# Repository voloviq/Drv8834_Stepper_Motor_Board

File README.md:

# Drv8834_Stepper_Motor_Board
Simple dump pcb and schematic - dump due to obtain 3d design of module

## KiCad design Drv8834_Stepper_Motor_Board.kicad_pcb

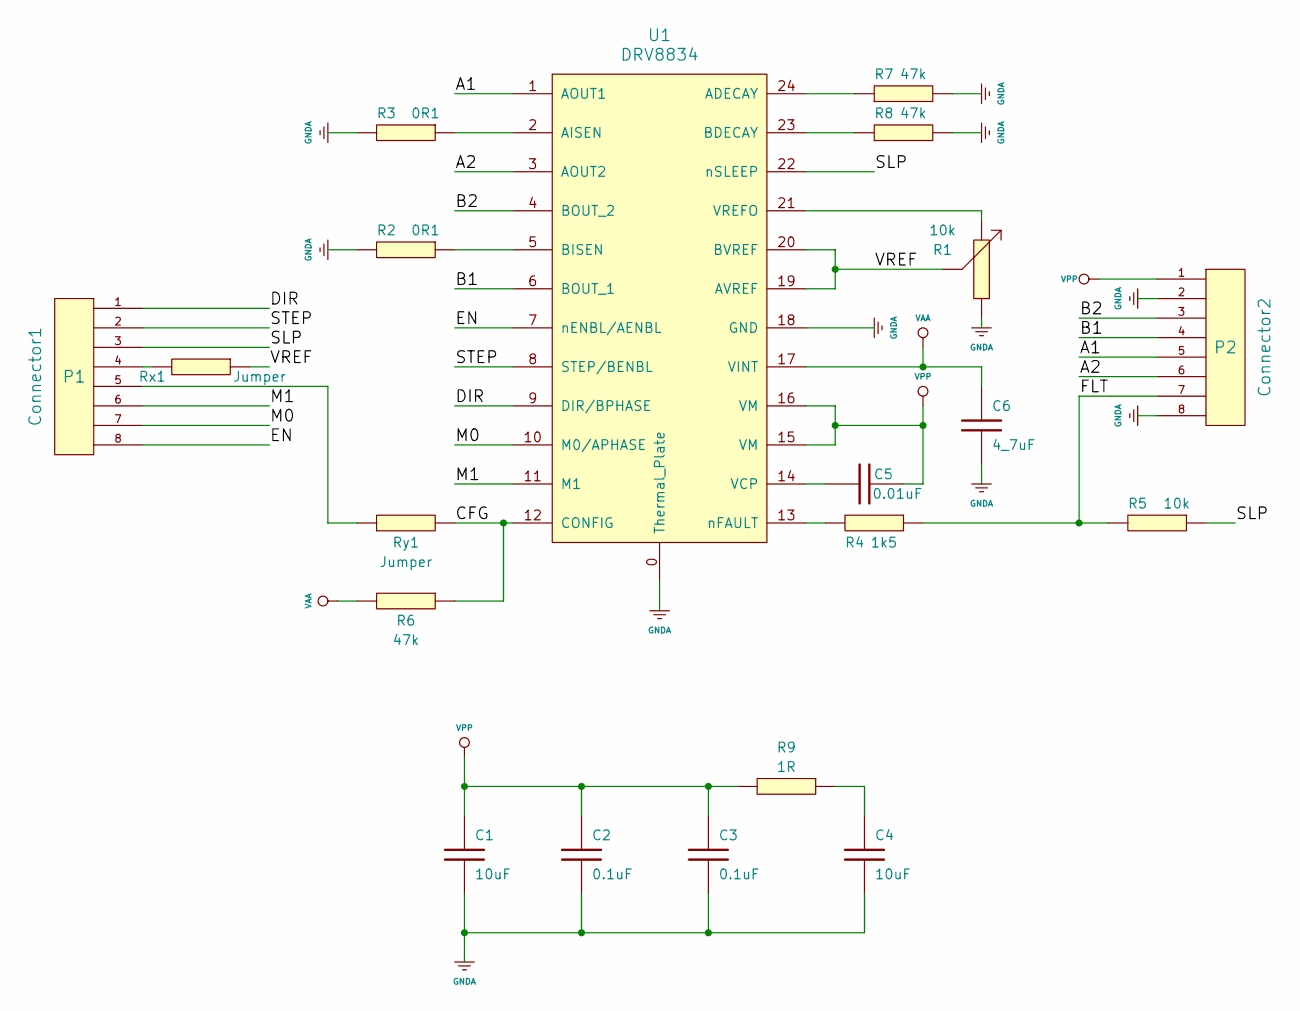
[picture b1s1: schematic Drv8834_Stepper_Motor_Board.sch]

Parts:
C1, C4: 10uF; 10uF_0805
C2, C3: 0.1uF; 100nF_0603
C5: 0.01uF; 1nF_0603
C6: 4_7uF; 4_7uF_0603
P1: Connector1; Goldpin_8_2_54mm
P2: Connector2; Goldpin_8_2_54mm
R1: 10k; 3364X-1-103E
R2, R3: 0R1; 0R1_1206
R4: 1k5; 1k5_0603
R5: 10k; 10k_0603
R6, R7, R8: 47k; 47k_0603
R9: 1R; 1R_0603
Rx1: Jumper; 0R_0603
Ry1: Jumper; 0R_0603
U1: DRV8834; DRV8834_QFN24

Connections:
/A1: P2.5, U1.1 (AOUT1)
/A2: P2.6, U1.3 (AOUT2)
/B1: P2.4, U1.6 (BOUT_1)
/B2: P2.3, U1.4 (BOUT_2)
/CFG: R6.1, Ry1.2, U1.12 (CONFIG)
/DIR: P1.1, U1.9 (DIR/BPHASE)
/EN: P1.8, U1.7 (nENBL/AENBL)
/FLT: P2.7, R4.1, R5.2
/M0: P1.7, U1.10 (M0/APHASE)
/M1: P1.6, U1.11 (M1)
/SLP: P1.3, R5.1, U1.22 (nSLEEP)
/STEP: P1.2, U1.8 (STEP/BENBL)
/VREF: R1.2, Rx1.1, U1.19 (AVREF), U1.20 (BVREF)
GNDA: C1.2, C2.2, C3.2, C4.2, C6.2, P2.2, P2.8, R1.1, R2.2, R3.2, R7.2, R8.2, U1.0 (Thermal_Plate), U1.18 (GND)
unnamed: C4.1, R9.1
unnamed: C5.1, U1.14 (VCP)
unnamed: P1.4, Rx1.2
unnamed: P1.5, Ry1.1
unnamed: R1.3, U1.21 (VREFO)
unnamed: R2.1, U1.5 (BISEN)
unnamed: R3.1, U1.2 (AISEN)
unnamed: R4.2, U1.13 (nFAULT)
unnamed: R7.1, U1.24 (ADECAY)
unnamed: R8.1, U1.23 (BDECAY)
VAA: C6.1, R6.2, U1.17 (VINT)
VPP: C1.1, C2.1, C3.1, C5.2, P2.1, R9.2, U1.15 (VM), U1.16 (VM)

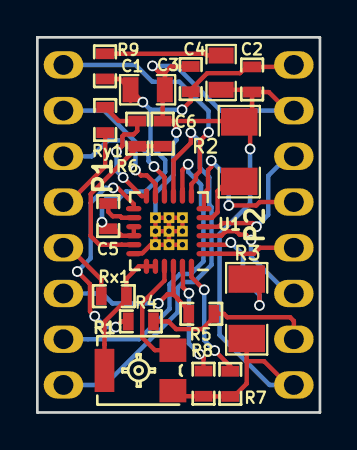
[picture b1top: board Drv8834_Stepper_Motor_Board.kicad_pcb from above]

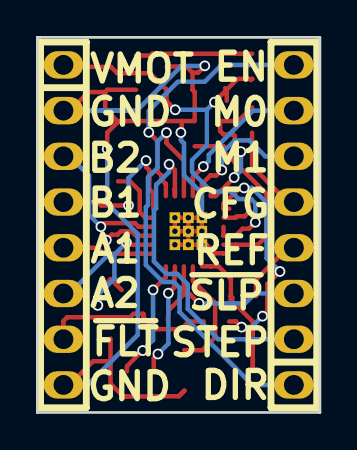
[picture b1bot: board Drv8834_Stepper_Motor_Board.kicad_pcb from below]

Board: 2 copper layers, 15.7 x 20.8 mm, 20 parts (2 on the bottom side), 26 nets.

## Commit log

2015-10-22 Initial issue of driver.
